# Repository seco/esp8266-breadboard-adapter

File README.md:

# esp8266-01 breadboard adapter
Adapter for esp8266-01 module to the breadboard.

*Designed by fu*

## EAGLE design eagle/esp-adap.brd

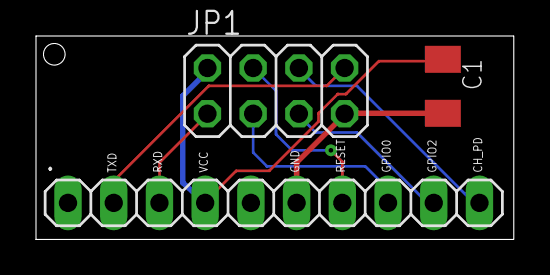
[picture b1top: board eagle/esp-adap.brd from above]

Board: 2 copper layers, 26.5 x 11.3 mm, 3 parts (0 on the bottom side), 8 nets.

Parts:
.: 1X10
C1: 100u; C1206K
JP1: 2X04

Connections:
CH_PD: ..10, JP1.6
GND: ..6, C1.2, JP1.7
GPIO0: ..8, JP1.3
GPIO2: ..9, JP1.5
RESET: ..7, JP1.4
RXD: ..3, JP1.1
TXD: ..2, JP1.8
VCC: ..4, C1.1, JP1.2

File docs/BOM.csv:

"Part","Value","Device","Package","Description",
"C1","100u","C-USC1206K","C1206K","CAPACITOR, American symbol",
"JP1","","PINHD-2X4","2X04","PIN HEADER",
"JP2","","PINHD-1X10","1X10","PIN HEADER",

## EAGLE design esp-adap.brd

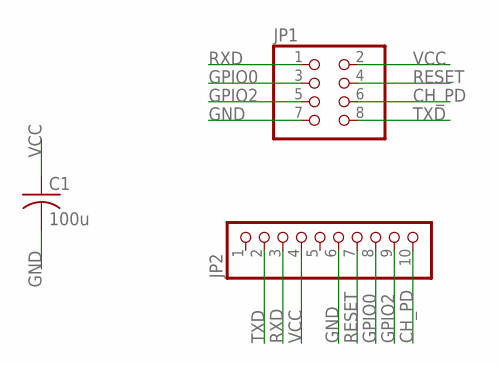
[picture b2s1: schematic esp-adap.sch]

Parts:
C1: 100u; C1206K
JP1: PINHD-2X4; 2X04
JP2: PINHD-1X10; 1X10

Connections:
CH_PD: JP1.6, JP2.10
GND: C1.2, JP1.7, JP2.6
GPIO0: JP1.3, JP2.8
GPIO2: JP1.5, JP2.9
RESET: JP1.4, JP2.7
RXD: JP1.1, JP2.3
TXD: JP1.8, JP2.2
VCC: C1.1, JP1.2, JP2.4

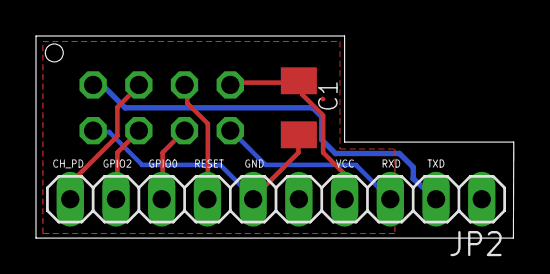
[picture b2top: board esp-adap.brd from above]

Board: 2 copper layers, 26.5 x 11.2 mm, 3 parts (1 on the bottom side), 8 nets.

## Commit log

2016-12-25 added netlist
2016-12-25 parts placed on pcb
2016-12-25 added cap to schematic
2016-12-25 begin 2nd layer pcb
2016-12-25 pcb almost finished
2016-12-26 pcb faces ok
2016-12-26 pcb finished
2016-12-26 pcb finished, added copper pour on both layers
2016-12-26 added images
2016-12-27 edited edge cuts
2016-12-27 added led on gpio2
2016-12-27 pcb complete
    pcb complete with signed bottom sikscreen
2016-12-27 plot
2016-12-27 img added
2016-12-27 missing footprint 10 pin header
2016-12-27 edited schematic
2016-12-28 new pcb layout, fix connection
2016-12-28 pcb complete
2016-12-28 added front silkscreen
2016-12-28 updated img
2016-12-28 updated img and silkscreen
2016-12-28 slightly updated pcb
2016-12-28 renamed img
2017-01-21 eagle version
2017-01-22 board done
2017-01-22 updated board
2017-01-22 added docs
2017-01-25 minor fix
2017-01-26 redefined board
2017-01-29 changed header
